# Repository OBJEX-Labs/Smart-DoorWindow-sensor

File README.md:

# Smart Door/Window sensor
The focus of this project is to prove how it is possible to drastically reduce the power consumption(in deep sleep/standby) of battery-powered smart devices by developing a customized power latch. Better design of smart devices would ensure a longer product life cycle.

## Power consumption

### Measurement range of PPK2
The current was measured with Nordic's power profiler kit , knowing that the current measured is less than the measurement range of this power profiler. I did several tests to verify the accuracy of the data. In any case the accuracy of the data, the consumption would be less than 200nA and this is a very good result considering that a similar device at a power consumption of 6-8uA.

### 1. Reed switch version
The consumption in deep sleep(POWER LATCH) is the same whether the magnet near the sensor or not.

### 2. MAGNETIC SENSOR IC(S-5701) version
deepsleep: 300nA

## 3D Case

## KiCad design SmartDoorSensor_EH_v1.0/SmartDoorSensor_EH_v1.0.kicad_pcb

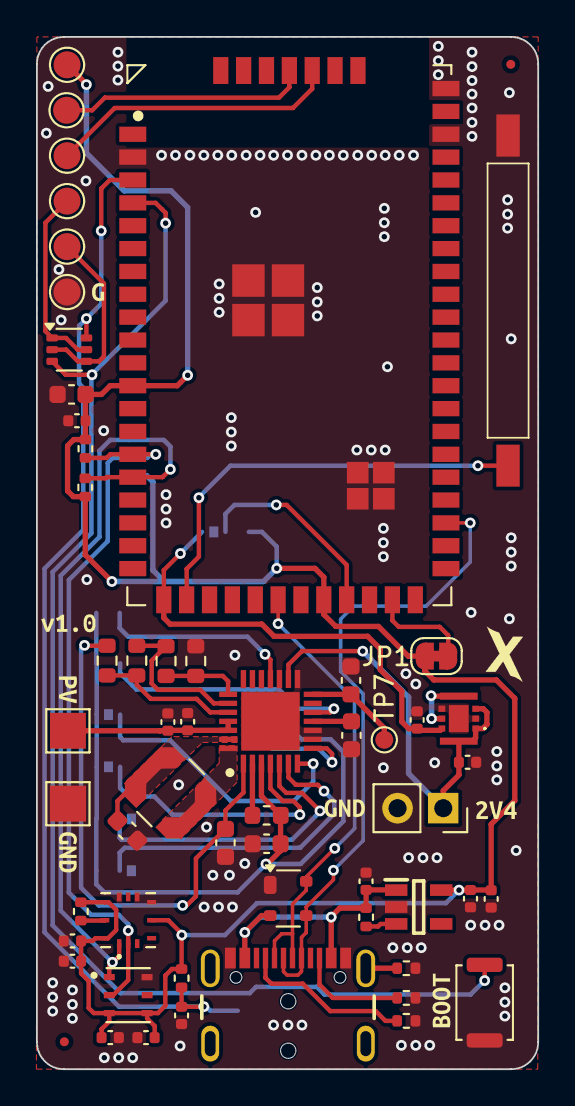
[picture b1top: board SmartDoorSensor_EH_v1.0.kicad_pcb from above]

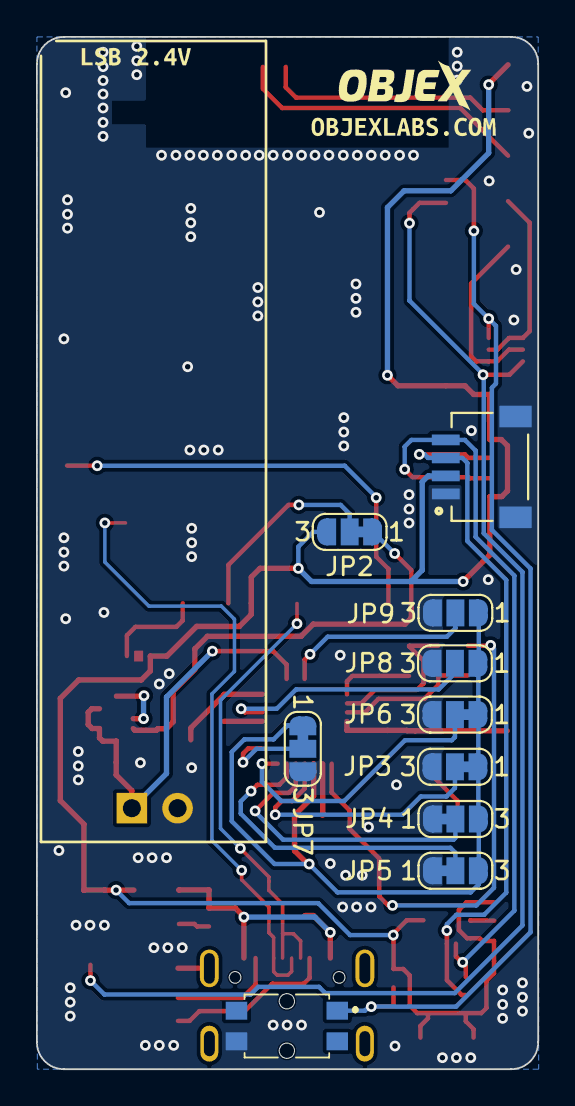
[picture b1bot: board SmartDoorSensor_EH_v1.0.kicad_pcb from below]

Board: 2 copper layers, 27.8 x 57.4 mm, 76 parts (12 on the bottom side), 42 nets.

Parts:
C1, C2, C7: 22uF; C_0603_1608Metric
C3, C4, C5: 10uF; C_0603_1608Metric
C6, C9, C11, C14, C17, C18: 10uF; C_0402_1005Metric
C8, C10, C19: 1uF; C_0402_1005Metric
C12, C13, C16: 0.1uF; C_0402_1005Metric
C15: 0.01uF; C_0402_1005Metric
D1: SP0503BAHT; SOT-143
FID1, FID2: Fiducial; Fiducial_0.5mm_Mask1mm
IC1: AEM10941-QFN; QFN50P500X500X90-29N-D
IC2: XCL103D333CR-G; XCL102D283CRG
IC3: RT9080-33GJ5; SOT94P280X100-5N
IC4: ZMOD4410AI1R
J1: SM04B-SRSS-TB(LF)(SN); JST_SM04B-SRSS-TB(LF)(SN)
J2: USB4105-GF-A; GCT_USB4105-GF-A
J3: LSB TERMINAL; PinSocket_1x02_P2.54mm_Vertical
JP1: SolderJumper_2_Bridged; SolderJumper-2_P1.3mm_Bridged_RoundedPad1.0x1.5mm
JP2, JP3, JP4, JP5, JP6, JP7: SolderJumper_3_Bridged12; SolderJumper-3_P1.3mm_Bridged12_RoundedPad1.0x1.5mm_NumberL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
JP8, JP9: SolderJumper_3_Open; SolderJumper-3_P1.3mm_Open_RoundedPad1.0x1.5mm_NumberLabels
L1: 10uH-MLZ1608M100WT; L_0603_1608Metric
L2: 10uH-LPS4012-103MRC; L_Coilcraft_LPS4018
Q1: MUN5211DW1; SOT-363_SC-70-6
R1, R4, R10, R11, R12: 10K; R_0402_1005Metric
R2: 1M; R_0402_1005Metric
R3, R9: 5.1K; R_0402_1005Metric
R5, R6, R7, R8: TBD; R_0603_1608Metric
S1: MDSM-4R-12-18; MDSM4R1218
S2: 436331045822
SW2: BOOT; SW_Push_SPST_NO_Alps_SKRK
TP1: PV; TestPoint_Pad_2.0x2.0mm
TP2: GND; TestPoint_Pad_2.0x2.0mm
TP7: TestPoint; TestPoint_Pad_D1.0mm
TP8: 3V3; TestPoint_Pad_D1.5mm
TP9: TX; TestPoint_Pad_D1.5mm
TP10: RX; TestPoint_Pad_D1.5mm
TP11: RTS; TestPoint_Pad_D1.5mm
TP12: DTR; TestPoint_Pad_D1.5mm
TP13: GND; TestPoint_Pad_D1.5mm
U1: HS3001; XDCR_HS3001
U2: ELPM-S3LW; ELPM-S3XX
kibuzzard-64D611C7: G***; kibuzzard-64D611C7
kibuzzard-667E7E0B: G***; kibuzzard-667E7E0B
kibuzzard-667E7E21, kibuzzard-667E7E21#2: G***; kibuzzard-667E7E21
kibuzzard-667E7EB7: G***; kibuzzard-667E7EB7
kibuzzard-667E862E: G***; kibuzzard-667E862E
kibuzzard-667956CB: G***; kibuzzard-667956CB
kibuzzard-667957A8: G***; kibuzzard-667957A8
kibuzzard-66795660: G***; kibuzzard-66795660

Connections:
+3V3: C7.1, C8.1, C10.1, C11.1, C12.1, C13.1, C14.1, C19.1, IC3.5 (VOUT), IC4.5 (VDD), IC4.10 (VDDH), IC4.12 (VDDIO), J1.2, JP1.1 (A), JP2.3 (B), R4.1, R10.1, R11.1, R12.1, TP8.1, U1.3 (VC), U1.4 (VDD), U2.11 (3V3_ESP), U2.27 (3V3_LORA)
+5V: C9.1, D1.2 (K), IC3.1 (VIN), J2.A4_B9 (VBUS), J2.B4_A9 (VBUS), R1.1
/ELPM-S3LW/D+: D1.3 (K), J2.A6 (DP1), J2.B6 (DP2), U2.34 (GPIO20)
/ELPM-S3LW/D-: D1.4 (K), J2.A7 (DN1), J2.B7 (DN2), U2.25 (GPIO19)
/ELPM-S3LW/DTR: Q1.2 (B2), Q1.4 (E1), TP12.1
/ELPM-S3LW/GPIO0: Q1.3 (C1), SW2.2, U2.3 (GPIO0)
/ELPM-S3LW/REED_Switch: S1.1, U2.21 (PLATCH_MASTER)
/ELPM-S3LW/RESET: C6.1, Q1.6 (C2), R4.2, S2.1 (COM_1), U2.2 (RESET)
/ELPM-S3LW/RTS: Q1.1 (E2), Q1.5 (B1), TP11.1
/ELPM-S3LW/RXD: TP10.1, U2.55 (RXD)
/ELPM-S3LW/SCL: IC4.1 (SCL), J1.4, R10.2, U1.1 (SCL), U2.15 (GPIO9/SCL)
/ELPM-S3LW/SDA: IC4.2 (SDA), J1.3, R11.2, U1.2 (SDA), U2.14 (GPIO8/SDA)
/ELPM-S3LW/TXD: TP9.1, U2.56 (TXD)
/ELPM-S3LW/VDD_RTC: JP2.2 (C), U2.28 (VDD_RTC)
/Energy Harvester - AEM10941/Boost: C1.2, IC1.1 (BOOST), R5.1
/Energy Harvester - AEM10941/CFG0: IC1.6 (CFG[0]), JP5.2 (C)
/Energy Harvester - AEM10941/CFG1: IC1.5 (CFG[1]), JP4.2 (C)
/Energy Harvester - AEM10941/CFG2: IC1.4 (CFG[2]), JP3.2 (C)
/Energy Harvester - AEM10941/CHRDY: IC1.23 (SET_CHRDY), R6.2, R7.1
/Energy Harvester - AEM10941/ENHV: IC1.12 (ENHV), JP8.2 (C)
/Energy Harvester - AEM10941/ENLV: IC1.18 (ENLV), JP9.2 (C)
/Energy Harvester - AEM10941/HVOUT: C5.1, IC1.14 (HVOUT), TP7.1
/Energy Harvester - AEM10941/LVOUT: C4.1, IC1.11 (LVOUT)
/Energy Harvester - AEM10941/OVCH: IC1.22 (SET_OVCH), R7.2, R8.1
/Energy Harvester - AEM10941/OVDIS: IC1.24 (SET_OVDIS), R5.2, R6.1
/Energy Harvester - AEM10941/PV_cell: C15.1, C16.1, IC1.25 (SRC), IC1.26 (FB_COLD), TP1.1
/Energy Harvester - AEM10941/SELMPP0: IC1.8 (SELMPP[0]), JP7.2 (C)
/Energy Harvester - AEM10941/SELMPP1: IC1.7 (SELMPP[1]), JP6.2 (C)
/Energy Harvester - AEM10941/Vbuck: C2.2, IC1.3 (BUCK), JP3.1 (A), JP4.3 (B), JP5.3 (B), JP6.1 (A), JP7.1 (A), JP8.1 (A), JP9.1 (A), L1.1
/LSB: C17.1, IC1.16 (BATT), IC2.1 (VBAT), IC2.3 (CE), IC2.7 (L1), J3.1
GND: C1.1, C2.1, C3.2, C4.2, C5.2, C6.2, C7.2, C8.2, C9.2, C10.2, C11.2, C12.2, C13.2, C14.2, C15.2, C16.2, C17.2, C18.2, C19.2, D1.1 (A), IC1.9 (FB_PRIM_D), IC1.10 (FB_PRIM_U), IC1.15 (BAL), IC1.17 (PRIM), IC1.29 (EP), IC2.2 (GND_1), IC2.4 (GND_2), IC2.9 (EP_GND), IC3.2 (GND), IC4.6 (VSS_1), IC4.7 (VSS_2), IC4.9 (VSS_3), J1.1, J1.S1 (SHIELD), J1.S2 (SHIELD), J2.A1_B12 (GND), J2.B1_A12 (GND), J3.2, JP3.3 (B), JP4.1 (A), JP5.1 (A), JP6.3 (B), JP7.3 (B), JP8.3 (B), JP9.3 (B), R2.2, R3.2, R8.2, R9.2, S1.2, S2.4 (NO_2), SW2.1, TP2.1, TP13.1, U1.6 (VSS), U2.1 (GND), U2.51 (GND), U2.52 (GND), U2.60 (GND), U2.61 (GND), U2.62 (GND), U2.63 (GND), U2.64 (GND), U2.65 (GND), U2.66 (GND), U2.67 (GND)
unnamed: C3.1, IC1.27 (BUFSRC), L2.1
unnamed: IC1.28 (SWBOOST), L2.2
unnamed: IC1.2 (SWBUCK), L1.2
unnamed: IC2.5 (LX), IC2.8 (L2)
unnamed: IC3.3 (EN), R1.2
unnamed: IC4.11 (RES_N), R12.2
unnamed: J2.A5 (CC1), R9.1
unnamed: J2.B5 (CC2), R3.1
unnamed: J2.S1 (SHELL_GND), J2.S2 (SHELL_GND), J2.S3 (SHELL_GND), J2.S4 (SHELL_GND), R2.1
unnamed: JP1.2 (B), U2.30 (PWR_LED)
VIN: C18.1, IC2.6 (VOUT), JP2.1 (A), U2.20 (VIN(3-5V))

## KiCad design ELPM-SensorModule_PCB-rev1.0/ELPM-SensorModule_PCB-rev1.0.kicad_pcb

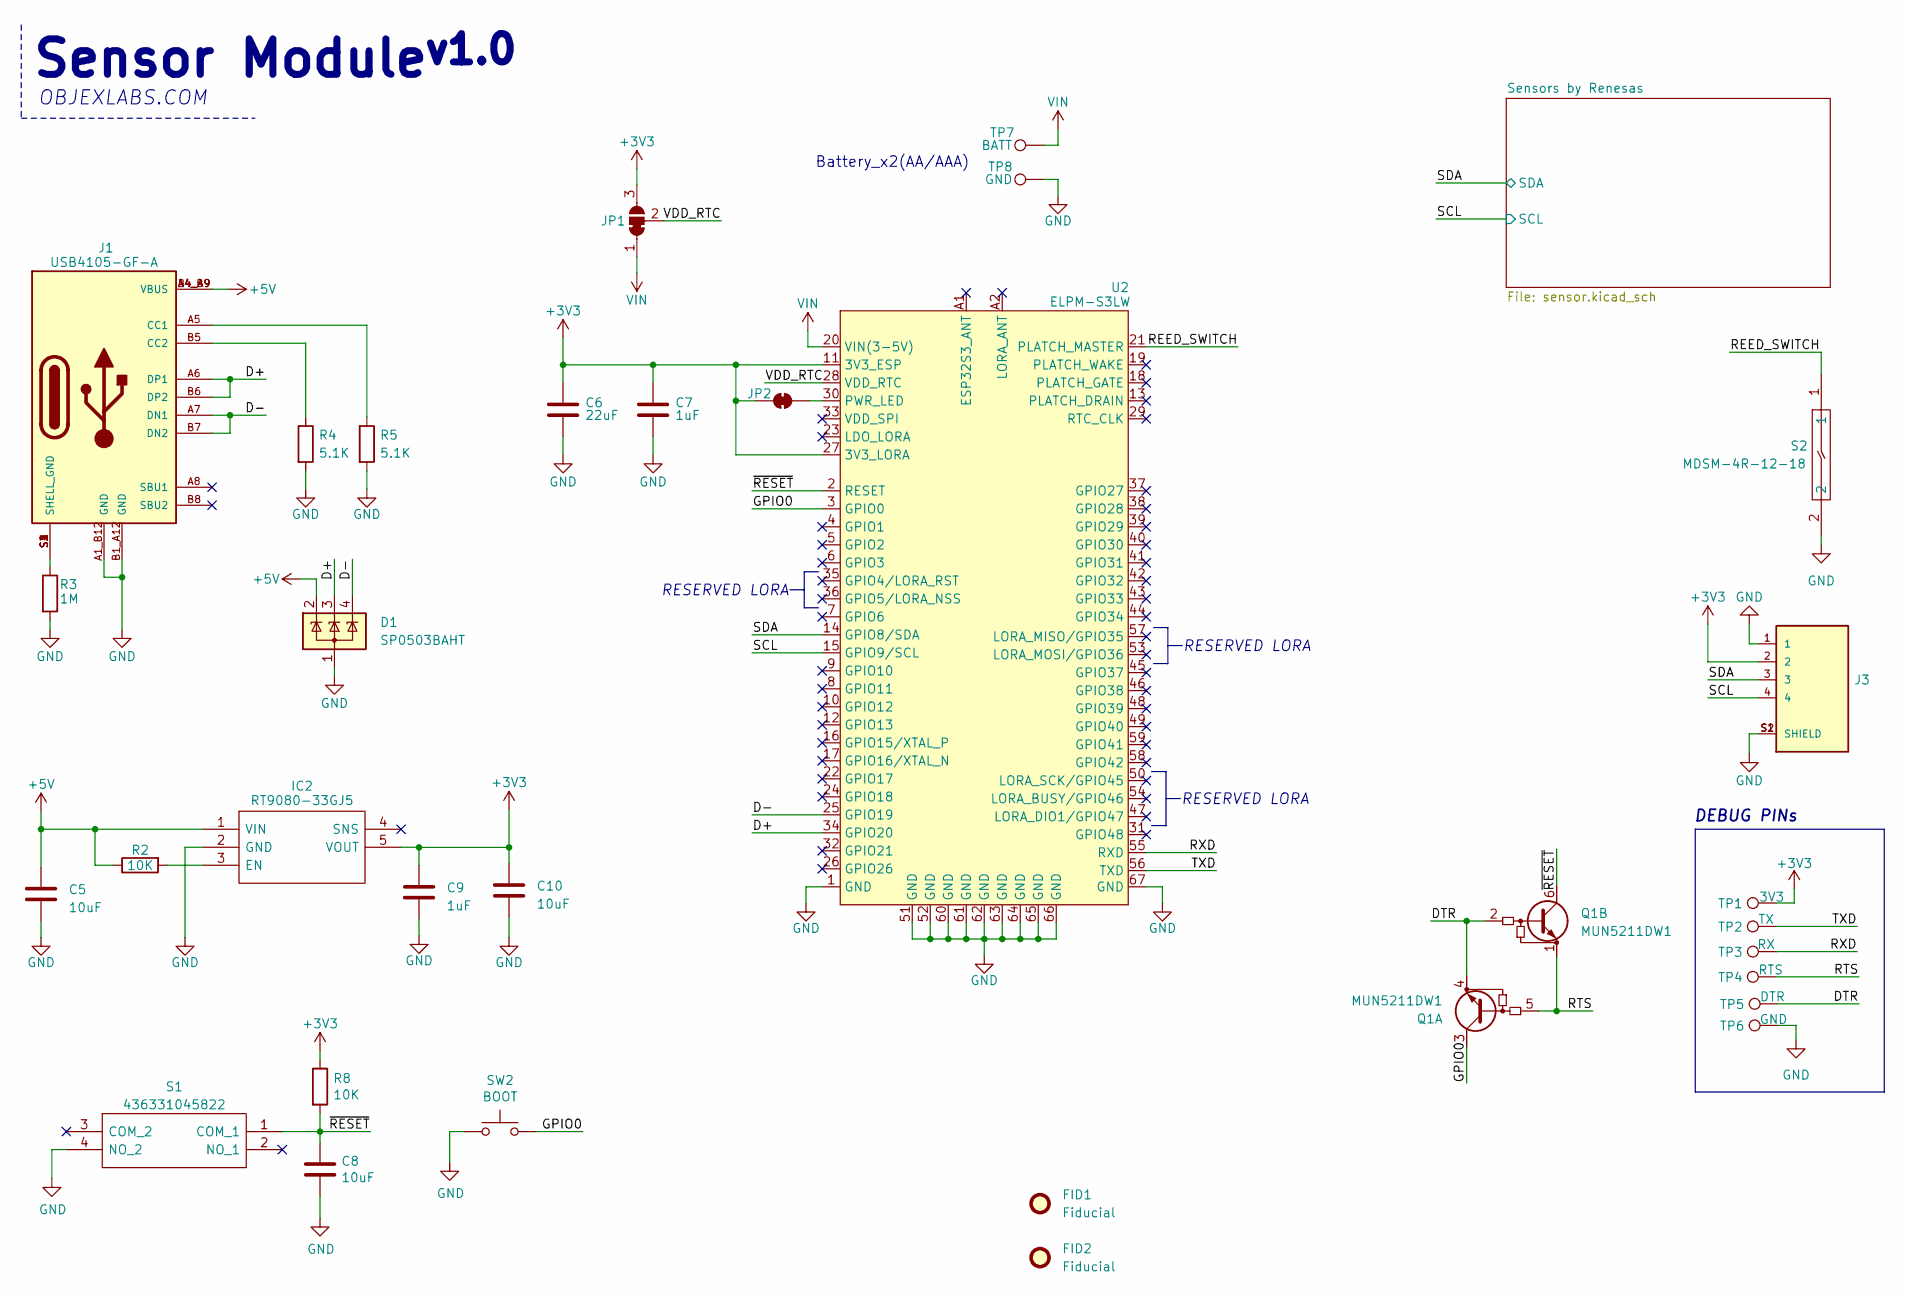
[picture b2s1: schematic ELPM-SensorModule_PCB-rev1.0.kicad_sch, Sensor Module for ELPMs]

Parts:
C5, C8, C10: 10uF; C_0402_1005Metric
C6: 22uF; C_0603_1608Metric
C7, C9: 1uF; C_0402_1005Metric
D1: SP0503BAHT; SOT-143
FID1, FID2: Fiducial; Fiducial_0.5mm_Mask1mm
IC2: RT9080-33GJ5; SOT94P280X100-5N; Manufacturer_Part_Number RT9080-33GJ5
J1: USB4105-GF-A; GCT_USB4105-GF-A; PARTREV A3
J3: SM04B-SRSS-TB(LF)(SN); JST_SM04B-SRSS-TB(LF)(SN)
JP1: SolderJumper_3_Bridged12; SolderJumper-3_P1.3mm_Bridged12_RoundedPad1.0x1.5mm_NumberL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
JP2: SolderJumper_2_Bridged; SolderJumper-2_P1.3mm_Bridged_RoundedPad1.0x1.5mm
Q1: MUN5211DW1; SOT-363_SC-70-6
R2, R8: 10K; R_0402_1005Metric
R3: 1M; R_0402_1005Metric
R4, R5: 5.1K; R_0402_1005Metric
S1: 436331045822; Mouser Part Number 710-436331045822
S2: MDSM-4R-12-18; MDSM4R1218; Mouser Part Number 934-MDSM-4R12-18
SW2: BOOT; SW_Push_SPST_NO_Alps_SKRK
TP1: 3V3; TestPoint_Pad_D1.5mm
TP2: TX; TestPoint_Pad_D1.5mm
TP3: RX; TestPoint_Pad_D1.5mm
TP4: RTS; TestPoint_Pad_D1.5mm
TP5: DTR; TestPoint_Pad_D1.5mm
TP6: GND; TestPoint_Pad_D1.5mm
TP7: BATT; TestPoint_Pad_2.0x2.0mm
TP8: GND; TestPoint_Pad_2.0x2.0mm
U2: ELPM-S3LW; ELPM-S3XX

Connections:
+3V3: C6.1, C7.1, C9.1, C10.1, IC2.5 (VOUT), J3.2, JP1.3 (B), JP2.1 (A), R8.1, TP1.1, U2.11 (3V3_ESP), U2.27 (3V3_LORA); also elsewhere on the board
+5V: C5.1, D1.2 (K), IC2.1 (VIN), J1.A4_B9 (VBUS), J1.B4_A9 (VBUS), R2.1
/D+: D1.3 (K), J1.A6 (DP1), J1.B6 (DP2), U2.34 (GPIO20)
/D-: D1.4 (K), J1.A7 (DN1), J1.B7 (DN2), U2.25 (GPIO19)
/DTR: Q1.2 (B2), Q1.4 (E1), TP5.1
/GPIO0: Q1.3 (C1), SW2.2, U2.3 (GPIO0)
/REED_SWITCH: S2.1, U2.21 (PLATCH_MASTER)
/RTS: Q1.1 (E2), Q1.5 (B1), TP4.1
/RXD: TP3.1, U2.55 (RXD)
/SCL: J3.4, U2.15 (GPIO9/SCL); also elsewhere on the board
/SDA: J3.3, U2.14 (GPIO8/SDA); also elsewhere on the board
/TXD: TP2.1, U2.56 (TXD)
/VDD_RTC: JP1.2 (C), U2.28 (VDD_RTC)
/~RESET: C8.1, Q1.6 (C2), R8.2, S1.1 (COM_1), U2.2 (RESET)
GND: C5.2, C6.2, C7.2, C8.2, C9.2, C10.2, D1.1 (A), IC2.2 (GND), J1.A1_B12 (GND), J1.B1_A12 (GND), J3.1, J3.S1 (SHIELD), J3.S2 (SHIELD), R3.2, R4.2, R5.2, S1.4 (NO_2), S2.2, SW2.1, TP6.1, TP8.1, U2.1 (GND), U2.51 (GND), U2.52 (GND), U2.60 (GND), U2.61 (GND), U2.62 (GND), U2.63 (GND), U2.64 (GND), U2.65 (GND), U2.66 (GND), U2.67 (GND); also elsewhere on the board
unnamed: IC2.3 (EN), R2.2
unnamed: J1.A5 (CC1), R5.1
unnamed: J1.B5 (CC2), R4.1
unnamed: J1.S1 (SHELL_GND), J1.S2 (SHELL_GND), J1.S3 (SHELL_GND), J1.S4 (SHELL_GND), R3.1
unnamed: JP2.2 (B), U2.30 (PWR_LED)
VIN: JP1.1 (A), TP7.1, U2.20 (VIN(3-5V))

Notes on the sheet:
RESERVED LORA
OBJEXLABS.COM
DEBUG PINs
Sensor Module^{v1.0}
Battery_x2(AA/AAA)

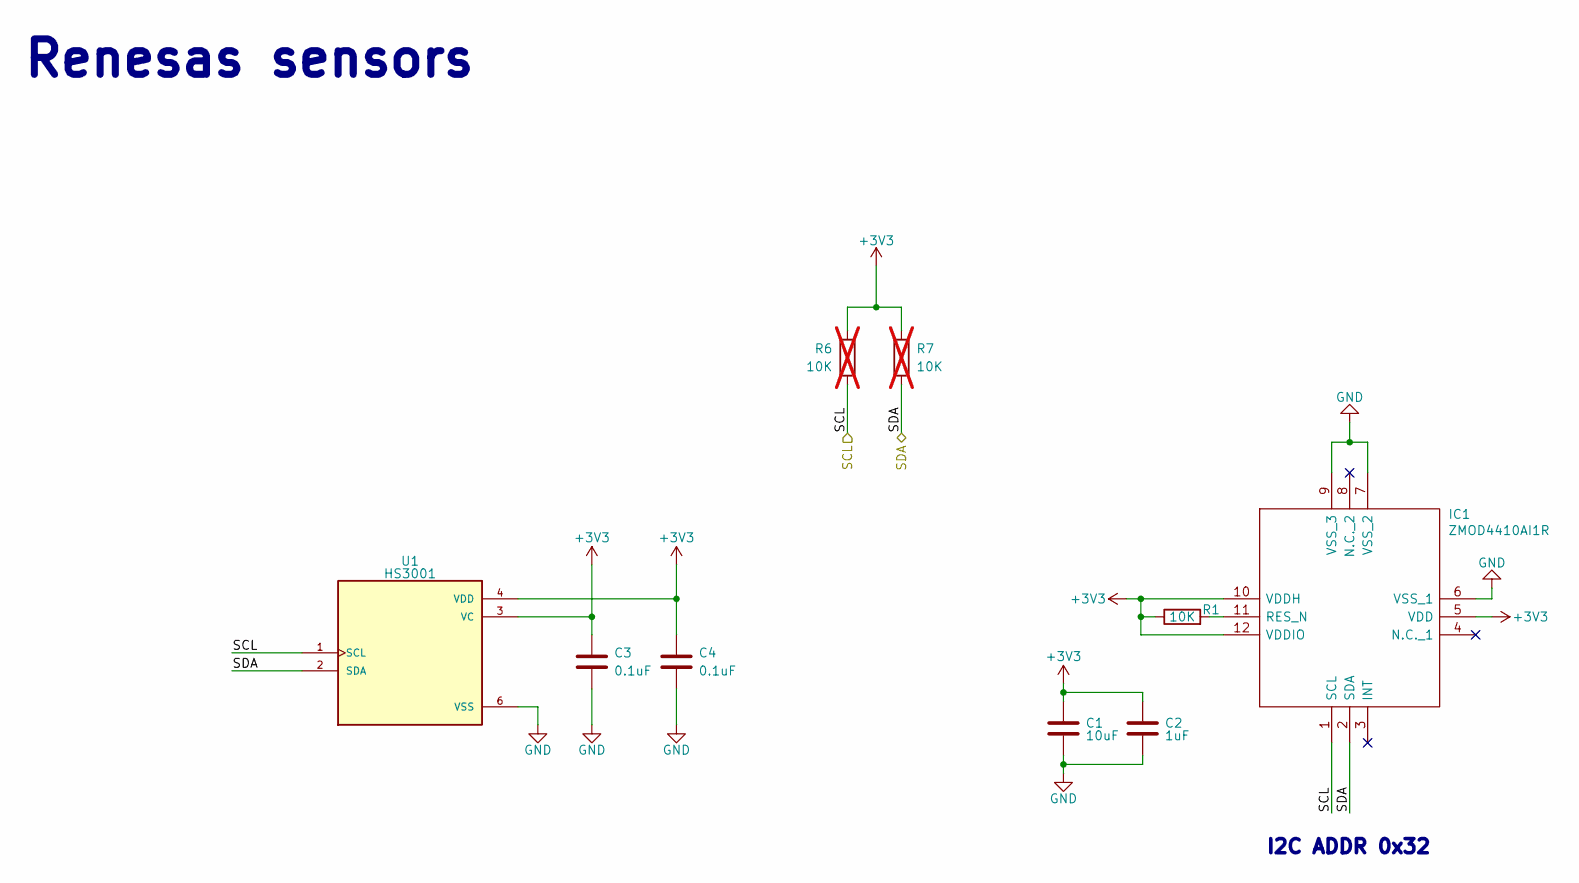
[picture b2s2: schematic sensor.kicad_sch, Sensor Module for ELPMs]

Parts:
C1: 10uF; C_0402_1005Metric
C2: 1uF; C_0402_1005Metric
C3, C4: 0.1uF; C_0402_1005Metric
IC1: ZMOD4410AI1R; Mouser Part Number 964-ZMOD4410AI1R
R1: 10K; R_0402_1005Metric
R6, R7: 10K; R_0402_1005Metric; not fitted
U1: HS3001; XDCR_HS3001; PARTREV August 6, 2018 (Rev 01)

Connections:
+3V3: C1.1, C2.1, C3.1, C4.1, IC1.5 (VDD), IC1.10 (VDDH), IC1.12 (VDDIO), R1.1, R6.1, R7.1, U1.3 (VC), U1.4 (VDD); also elsewhere on the board
/SCL: IC1.1 (SCL), R6.2, U1.1 (SCL); also elsewhere on the board
/SDA: IC1.2 (SDA), R7.2, U1.2 (SDA); also elsewhere on the board
GND: C1.2, C2.2, C3.2, C4.2, IC1.6 (VSS_1), IC1.7 (VSS_2), IC1.9 (VSS_3), U1.6 (VSS); also elsewhere on the board
unnamed: IC1.11 (RES_N), R1.2

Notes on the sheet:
Renesas sensors
I2C ADDR 0x32

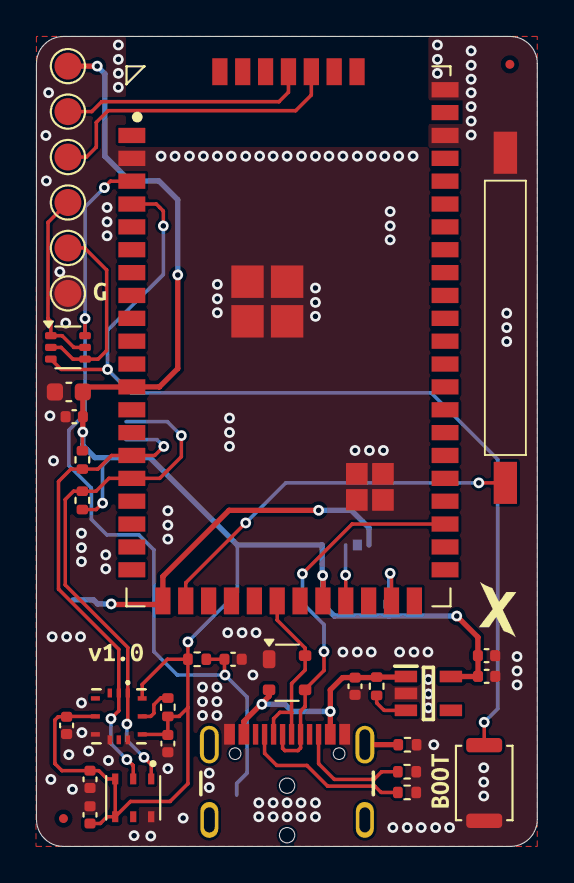
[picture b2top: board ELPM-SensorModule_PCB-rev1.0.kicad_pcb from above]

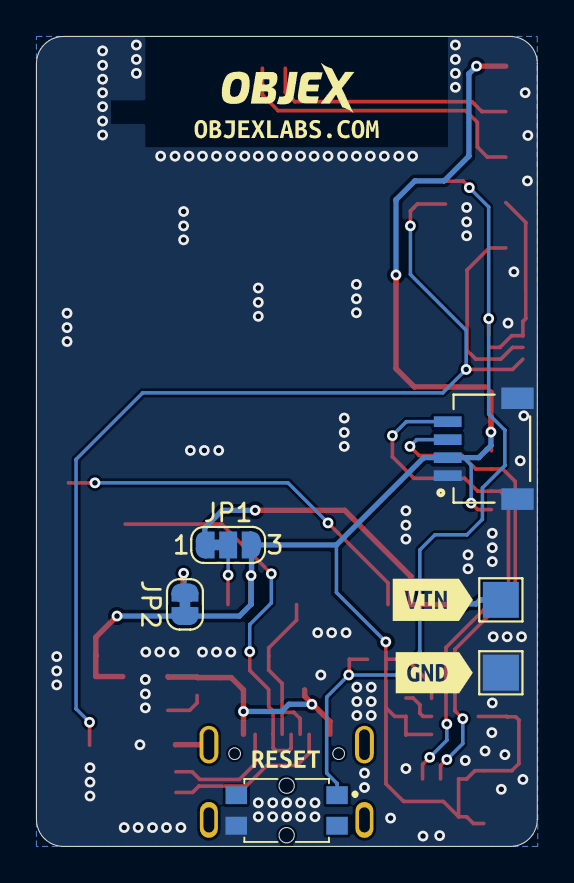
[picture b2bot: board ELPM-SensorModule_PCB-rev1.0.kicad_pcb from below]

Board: 2 copper layers, 27.8 x 45.0 mm, 48 parts (10 on the bottom side), 22 nets.

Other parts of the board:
kibuzzard-64D611C7: G***; kibuzzard-64D611C7
kibuzzard-6676ECD5: G***; kibuzzard-6676ECD5
kibuzzard-667956CB: G***; kibuzzard-667956CB
kibuzzard-667956E6: G***; kibuzzard-667956E6
kibuzzard-667957A8: G***; kibuzzard-667957A8
kibuzzard-66795660: G***; kibuzzard-66795660
kibuzzard-66795678: G***; kibuzzard-66795678

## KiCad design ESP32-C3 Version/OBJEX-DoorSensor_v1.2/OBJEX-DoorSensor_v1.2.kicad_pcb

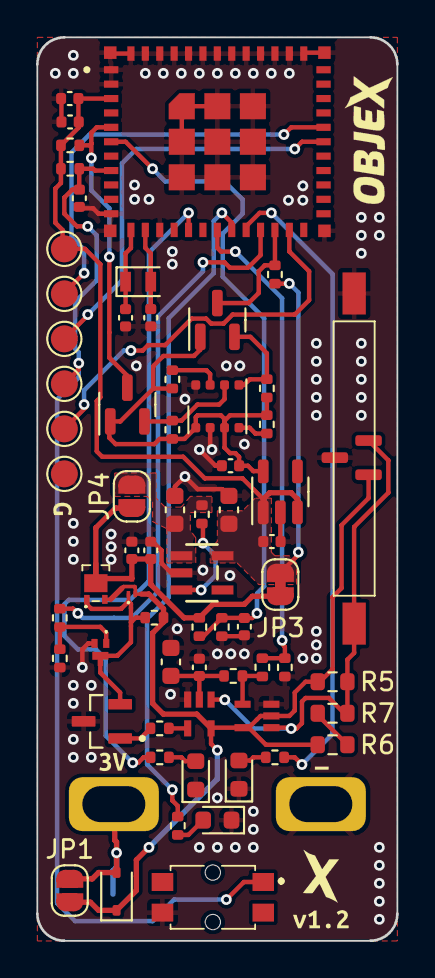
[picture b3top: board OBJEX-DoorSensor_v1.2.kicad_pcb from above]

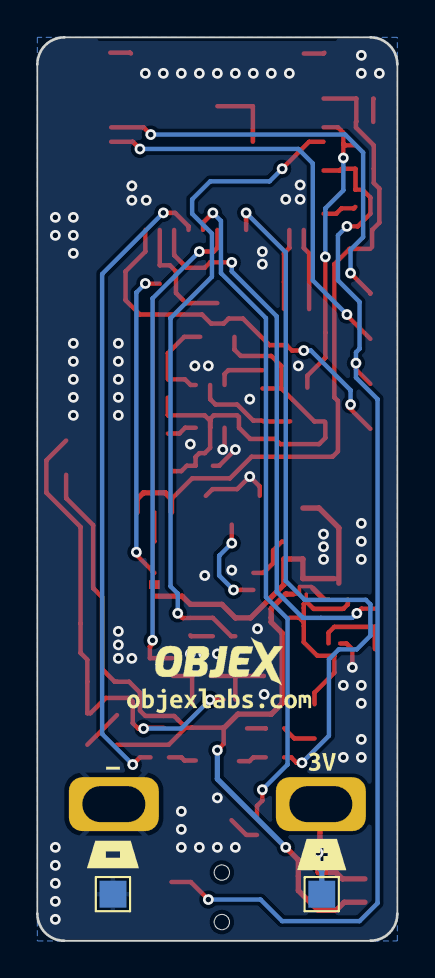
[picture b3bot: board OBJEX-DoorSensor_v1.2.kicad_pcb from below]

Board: 2 copper layers, 20.0 x 50.2 mm, 79 parts (7 on the bottom side), 37 nets.

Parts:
C1, C4, C9, C12: 10uF; C_0402_1005Metric
C2, C3: 12pF; C_0402_1005Metric
C5: 0.1uF; C_0402_1005Metric
C6: 1uF; C_0603_1608Metric
C7: 1uF/4.7uF; C_0603_1608Metric
C8: 10uF; C_0603_1608Metric
C10, C14, C15: 1uF; C_0402_1005Metric
C11: 10nF; C_0402_1005Metric
D1: RED; LED_0603_1608Metric
D2: GREEN; LED_0603_1608Metric
D3: BLUE; LED_0603_1608Metric
D5: 1N4148WS; D_SOD-323
JP1, JP4: SolderJumper_2_Open; SolderJumper-2_P1.3mm_Open_RoundedPad1.0x1.5mm
JP3: SolderJumper_2_Bridged; SolderJumper-2_P1.3mm_Bridged_RoundedPad1.0x1.5mm
Q1: BC857B_RF; SOT95P237X112-3N
Q2: NTNUS3171PZT5G; ONSC-SOT-1123-3-524AA_V
Q3: 2N7002KQBZ
Q4, Q5: BSS138; SOT-23
Q6: DMG3415UFY4Q-7; DMG3415UFY47
R1, R2, R4, R8, R9, R10, R12, R15, R16, R17, R18, R19: 10K; R_0402_1005Metric
R3, R20, R21, R23: 1K; R_0402_1005Metric
R5: 100M; R_0603_1608Metric
R6, R7: R; R_0603_1608Metric
R11: 1M; R_0402_1005Metric
R13, R22: 100K; R_0402_1005Metric
R14: 150K; R_0402_1005Metric
S1: MDSM-4R-12-18; MDSM4R1218
S2: 436331045822
TP1: BATT; TestPoint_Pad_1.5x1.5mm
TP2: GND; TestPoint_Pad_1.5x1.5mm
TP3: VBUS; TestPoint_Pad_D1.5mm
TP4: TX; TestPoint_Pad_D1.5mm
TP5: RX; TestPoint_Pad_D1.5mm
TP6: RTS; TestPoint_Pad_D1.5mm
TP7: DTR; TestPoint_Pad_D1.5mm
TP8: GND; TestPoint_Pad_D1.5mm
U1: 5204
U2: RT9080-33GJ5; TSOT-23
U3: S-5701BC11B-L3T2U5; S'5701BC11B'L3T2U5
U4, U5: SN74LVC1G86DBVR; SOT353
U6: BME680; Bosch_LGA-8_3x3mm_P0.8mm_ClockwisePinNumbering
U7: ESP32-C3-MINI-1-N4; XCVR_ESP32-C3-MINI-1-N4
U8: MCP1802T-1802I/OT; SOT-23-5
U10: 5226
Y1: Crystal; Crystal_SMD_2012-2Pin_2.0x1.2mm
kibuzzard-63AF0800: G***; kibuzzard-63AF0800
kibuzzard-642BF0F2: G***; kibuzzard-642BF0F2
kibuzzard-642BF081: G***; kibuzzard-642BF081
kibuzzard-64258E17, kibuzzard-64258E17#2: G***; kibuzzard-64258E17
kibuzzard-64258E23, kibuzzard-64258E23#2: G***; kibuzzard-64258E23
kibuzzard-64258E65: G***; kibuzzard-64258E65
kibuzzard-64258FE0: G***; kibuzzard-64258FE0

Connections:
+1V8: C14.1, Q4.1 (G), Q5.1 (G), R15.1, R16.1, R17.1, R18.1, U6.6 (VDDIO), U6.8 (VDD), U8.5 (VOUT)
+3V3: C4.1, C5.1, C7.2, C15.1, JP3.2 (B), R1.1, R2.2, R19.2, TP3.1, U2.5 (VOUT), U7.3 (3V3), U8.1 (VIN), U8.3 (~SHDN)
+BATT: D5.1 (K), JP1.2 (B), Q2.2, Q6.2, R5.1, R6.1, R11.1, U3.2 (VDD), U4.2 (B), U4.5 (VCC), U5.5 (VCC)
/Microcontroller + WiFi-BLE/AUTO_TURN_OFF: R12.2, U7.21 (IO7)
/Microcontroller + WiFi-BLE/BATT_LVL: C11.1, R13.2, R14.1, U7.6 (IO3)
/Microcontroller + WiFi-BLE/DTR/GPIO9: TP7.1, U7.23 (IO9)
/Microcontroller + WiFi-BLE/EN: C1.1, R1.2, S2.1 (COM_1), TP6.1, U7.8 (EN)
/Microcontroller + WiFi-BLE/GPIO0: C2.1, U7.12 (IO0), Y1.1
/Microcontroller + WiFi-BLE/GPIO1: C3.1, U7.13 (IO1), Y1.2
/Microcontroller + WiFi-BLE/GPIO2: Q5.3 (D), R19.1, U7.5 (IO2)
/Microcontroller + WiFi-BLE/GPIO8: Q4.3 (D), R2.1, U7.22 (IO8)
/Microcontroller + WiFi-BLE/IN_STATUS: R8.2, R9.1, U7.18 (IO4)
/Microcontroller + WiFi-BLE/LED_BLUE: R21.2, U7.19 (IO5)
/Microcontroller + WiFi-BLE/LED_GREEN: R20.2, U7.16 (IO10)
/Microcontroller + WiFi-BLE/LED_RED: R3.2, U7.20 (IO6)
/Microcontroller + WiFi-BLE/RX/GPIO20: TP5.1, U7.30 (RXD0)
/Microcontroller + WiFi-BLE/TX/GPIO21: TP4.1, U7.31 (TXD0)
/Power Latch - Rising & falling edge detector /Gate: Q1.2, Q2.1, Q3.3, Q3.4, Q6.1, R11.2
GND: C1.2, C2.2, C3.2, C4.2, C5.2, C6.2, C7.1, C8.2, C9.2, C10.2, C11.2, C12.2, C14.2, C15.2, D1.1 (K), D2.1 (K), D3.1 (K), Q1.3, Q3.2, R9.2, R14.2, R22.2, S1.2, S2.4 (NO_2), TP2.1, TP8.1, U1.1 (-), U2.2 (GND), U3.1 (GND), U4.3 (VEE), U5.3 (VEE), U6.1 (GND), U6.7 (GND), U7.1 (GND), U7.2 (GND), U7.11 (GND), U7.14 (GND), U7.36 (GND), U7.37 (GND), U7.38 (GND), U7.39 (GND), U7.40 (GND), U7.41 (GND), U7.42 (GND), U7.43 (GND), U7.44 (GND), U7.45 (GND), U7.46 (GND), U7.47 (GND), U7.48 (GND), U7.49_1 (GND), U7.49_2 (GND), U7.49_3 (GND), U7.49_4 (GND), U7.49_5 (GND), U7.49_6 (GND), U7.49_7 (GND), U7.49_8 (GND), U7.49_9 (GND), U7.50 (GND), U7.51 (GND), U7.52 (GND), U7.53 (GND), U8.2 (GND)
unnamed: D1.2 (A), R3.1
unnamed: D2.2 (A), R20.1
unnamed: D3.2 (A), R21.1
unnamed: D5.2 (A), JP1.1 (A), TP1.1, U10.1 (+)
unnamed: C9.1, C10.1, JP3.1 (A), JP4.1 (A), Q2.3, Q6.3, R13.1
unnamed: Q1.1, R23.2
unnamed: Q3.1, R12.1, R22.1
unnamed: Q4.2 (S), R18.2, U6.4 (SCK)
unnamed: Q5.2 (S), R17.2, U6.3 (SDI)
unnamed: R6.2, R7.1
unnamed: R4.1, U2.3 (EN)
unnamed: R5.2, R7.2, S1.1, U3.3 (OUT), U4.1 (A), U5.1 (A)
unnamed: R8.1, R10.1, U4.4 (Y)
unnamed: C8.1, C12.1, R10.2, U5.2 (B)
unnamed: R23.1, U5.4 (Y)
unnamed: R16.2, U6.2 (CSB)
unnamed: R15.2, U6.5 (SDO)
VCC: C6.1, JP4.2 (B), R4.2, U2.1 (VIN)

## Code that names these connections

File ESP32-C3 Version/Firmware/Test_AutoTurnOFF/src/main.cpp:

#include <Arduino.h>

int AUTO_TURN_OFF = 7;

int LED_RED = 6;
int LED_GREEN = 10;
int LED_BLUE = 5;

int IN_STATUS = 4;

void setup() {
  Serial.begin(115200);

  pinMode(AUTO_TURN_OFF, OUTPUT);
  digitalWrite(AUTO_TURN_OFF, HIGH);

  pinMode(LED_RED, OUTPUT);
  pinMode(LED_GREEN, OUTPUT);
  pinMode(LED_BLUE, OUTPUT);

  Serial.println("AUTO TURN OFF");
}

void loop() {
  digitalWrite(LED_RED, HIGH);
  digitalWrite(AUTO_TURN_OFF, HIGH);
  delay(5000);
  Serial.println("SLEEP");
  digitalWrite(LED_RED, LOW);
  digitalWrite(AUTO_TURN_OFF,LOW);
}

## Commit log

2023-03-23 init
2023-03-24 SCH complate
2023-03-27 Ready for components placing
2023-03-30 Start PCB design
2023-04-04 Ready for last review
2023-04-05 last review
2023-04-06 Ready for order
2023-04-07 Final review - ready for production
2023-04-25 bug fix
2023-06-05 Update todo
2023-06-22 Revert "update"
2024-09-07 update, new version

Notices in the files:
ESP32-C3 Version/OBJEX-DoorSensor_v1.2/OBJEX-DoorSensor_v1.2.kicad_pcb:
Copyright CERN 2020.
This source describes Open Hardware and is licensed under the CERN-OHLW v2
using it under the terms of the CERN-OHL-W v2 (https:/cern.ch/cern-ohl).
